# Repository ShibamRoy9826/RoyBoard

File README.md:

# RoyBoard 

## Description

Its a mechanical keyboard that I made from scratch! Its basically a 75% tenkeyless keyboard with 81 keys in total, with 3 additional rotary encoders for different tasks such as volume control, brightness control and scrolling, of course these functionalities are subject to change. It has a few neopixels too! not per key RGB though, because i rarely use backlight and it was pretty daunting to route them up, considering the fact that i just started hardware back then, the ones which I have are meant for aesthetics. Currently, I have dropped the plan to solder them because I mirrored the pinouts and it will be a terrible mess to solder them, I guess I am still satisfied with how it turned out though. 

## Features 

- ~Includes RGB lights (not per key RGB)~ (Not soldered)
- Has 3 rotary encoders for different functions
    - Media playback
    - Brightness
    - Volume
    - Scrolling
    - DWM tag switching(Any other wm works)
- 2 Layer keyboard (as of now, may add more in future if needed)
- Consists of 81 keys in total + 3 clickable rotary encoders, a 75%-ish Tenkeyless keyboard
- 5 degree tilt stand for a comfortable typing experience

## Real Life Pics

## Renders

Just for reference, these are the original keycaps that I would be using: [here](https://curiositycaps.in/products/vintage-poker-translucent-keycaps-set) . I changed the keycaps later on, thus the renders use a different keycap set.

### Full 3d renders (To Be Updated)
The renders don't include stand yet, as it has been recently included. I will update the repo soon.

### Bottom case

### Top plate

### Stand

### PCB 3D (Front)

### PCB 3D (Back)

### Schematic

### Layout

### PCB

### PCB Back

### PCB Front

## What tools did I use? 

- [kiCad](https://www.kicad.org/) : For PCB designing
- [shapr3d](https://www.shapr3d.com/) (Mostly) & [OnShape](https://onshape.com): For Case designing
- [keyboard-layout-editor](keyboard-layout-editor.com): For layout designing

## Firmware
Written in QMK, I have shifted the firmware to another repository, so please check that out [here](https://github.com/ShibamRoy9826/RoyBoard-firmware)

## 3D models

You can check the 3d models out in this [public document of OnShape](https://cad.onshape.com/documents/ddc280e53ddd9ad94dbb1da3/w/e89386a56beb1bd36360f18a/e/ed9d1e719b4e163eef3ebe0b?renderMode=0&uiState=6905da6719ceb1e5cc223bec)

## Dimensions

The entire keyboard is **385.65mm** x **166mm** (153 without the branding part) x **13mm**(+13.527mm with stand)

## Bill of materials

| Item name                             |   Net Price(USD) |   Net Price(INR) |   Expected Net Price (INR) |   Diff (INR) |
|:--------------------------------------|-----------------:|-----------------:|---------------------------:|-------------:|
| Vintage Poker Translucent Keycaps Set |            18.2  |          1599    |                    1615.98 |       -16.98 |
| Raspberry PI PICO                     |             5.06 |           449    |                     449.28 |        -0.28 |
| 1N4148 THT Diodes                     |             2.13 |           189    |                     189.12 |        -0.12 |
| EC11 Rotary Encoders                  |             4.48 |           406    |                     397.78 |         8.22 |
| Gateron Weightlessness Switches       |            39.53 |          3510    |                    3509.87 |         0.13 |
| Durock Smokey Screw-In Stabilizers v2 |            18.13 |          1595    |                    1609.76 |       -14.76 |
| PCB                                   |            66    |          5860    |                    5860.14 |        -0.14 |
| SK6812 MINI-E LEDs                    |             7.62 |           669.59 |                     676.58 |        -6.99 |
| M2 x 6 mm Heat inserts                |             1.29 |           114.6  |                     114.54 |         0.06 |
| M2 x 6 mm screws                      |           nan    |           nan    |                     nan    |       nan    |
| 3D Prints                             |           nan    |           nan    |                     nan    |       nan    |

**Total:** $162.44 (14,423 INR)

## To-Do 
- [x] ~Build it irl~
- [x] ~Do testing~
- [x] ~Upload new pics here~

## Contributing

Everyone is welcome to contribute to the code!
You can also raise an issue, or suggest any features that you think would be great :)

## License
Licensed under the MIT License. See [LICENSE](LICENSE) for more information.

> ✨ Please star this repository if you liked this project 😁

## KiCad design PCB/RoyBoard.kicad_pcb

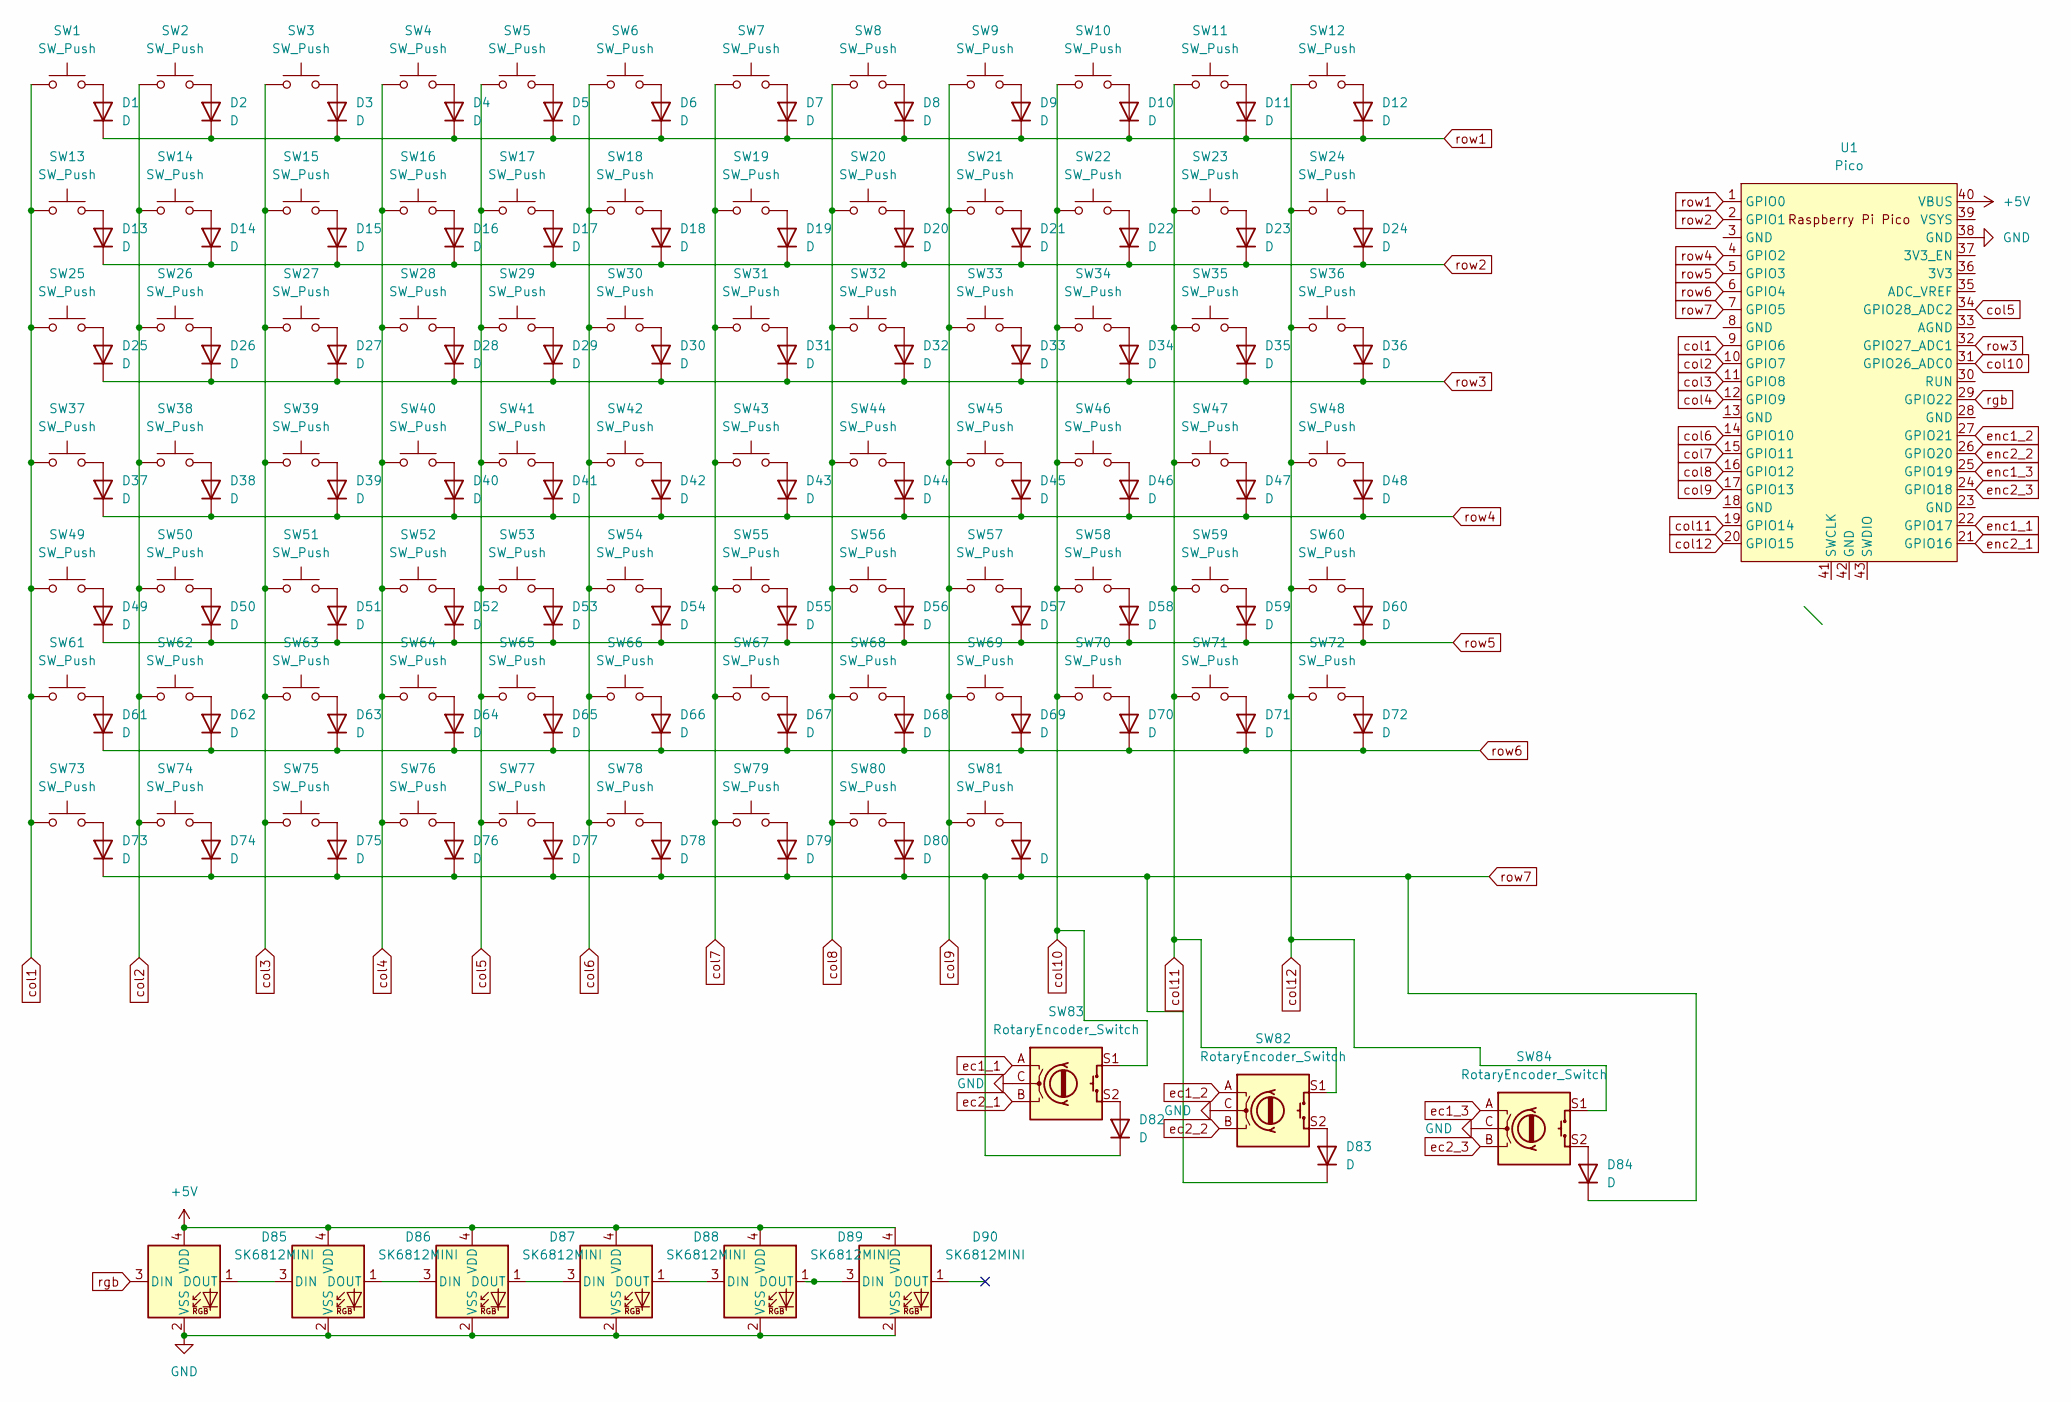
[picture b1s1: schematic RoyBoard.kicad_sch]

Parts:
D1, D2, D3, D4, D5, D6, D7, D8, D9, D10, D11, D12, D13, D14, D15, D16, D17, D18, D19, D20, D21, D22, D23, D24, D25, D26, D27, D28, D29, D30, D31, D32, D33, D34, D35, D36, D37, D38, D39, D40, D41, D42, D43, D44, D45, D46, D47, D48, D49, D50, D51, D52, D53, D54, D55, D56, D57, D58, D59, D60, D61, D62, D63, D64, D65, D66, D67, D68, D69, D70, D71, D72, D73, D74, D75, D76, D77, D78, D79, D80, D81, D82, D83, D84: D; Diode_DO-35
D85, D86, D87, D88, D89, D90: SK6812MINI; LED_SK6812MINI_PLCC4_3.5x3.5mm_P1.75mm
SW1, SW2, SW3, SW4, SW5, SW6, SW7, SW8, SW9, SW10, SW11, SW12, SW13, SW14, SW15, SW16, SW17, SW18, SW19, SW20, SW21, SW22, SW23, SW24, SW25, SW26, SW29, SW30, SW31, SW32, SW33, SW34, SW35, SW36, SW37, SW38, SW39, SW40, SW43, SW44, SW45, SW46, SW47, SW48, SW49, SW50, SW51, SW52, SW53, SW56, SW57, SW58, SW59, SW60, SW61, SW62, SW63, SW64, SW65, SW75, SW76, SW77, SW78, SW79, SW80, SW81: SW_Push; SW_Cherry_MX_1.00u_PCB
SW27: SW_Push; SW_Cherry_MX_PCB_2.00u
SW28, SW41: SW_Push; SW_Cherry_MX_PCB_1.50u
SW42: SW_Push; SW_Cherry_MX_PCB_1.75u
SW54, SW55: SW_Push; SW_Cherry_MX_2.25u_PCB
SW66: SW_Push; SW_Cherry_MX_2.75u_PCB
SW67: SW_Push; SW_Cherry_MX_1.25u_PCB
SW68, SW69, SW71, SW72, SW73, SW74: SW_Push; SW_Cherry_MX_PCB_1.25u
SW70: SW_Push; SW_Cherry_MX_6.25u_PCB
SW82, SW83, SW84: RotaryEncoder_Switch; RotaryEncoder_Alps_EC12E-Switch_Vertical_H20mm_CircularMoun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
U1: Pico; RPi_Pico_SMD_TH

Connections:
+5V: D85.4 (VDD), D86.4 (VDD), D87.4 (VDD), D88.4 (VDD), D89.4 (VDD), D90.4 (VDD), U1.40 (VBUS)
GND: D85.2 (VSS), D86.2 (VSS), D87.2 (VSS), D88.2 (VSS), D89.2 (VSS), D90.2 (VSS), SW82.C, SW83.C, SW84.C, U1.38 (GND)
unnamed: D1.2 (A), SW1.2
unnamed: D2.2 (A), SW2.2
unnamed: D3.2 (A), SW3.2
unnamed: D4.2 (A), SW4.2
unnamed: D5.2 (A), SW5.2
unnamed: D6.2 (A), SW6.2
unnamed: D7.2 (A), SW7.2
unnamed: D8.2 (A), SW8.2
unnamed: D9.2 (A), SW9.2
unnamed: D10.2 (A), SW10.2
unnamed: D11.2 (A), SW11.2
unnamed: D12.2 (A), SW12.2
unnamed: D13.2 (A), SW13.2
unnamed: D14.2 (A), SW14.2
unnamed: D15.2 (A), SW15.2
unnamed: D16.2 (A), SW16.2
unnamed: D17.2 (A), SW17.2
unnamed: D18.2 (A), SW18.2
unnamed: D19.2 (A), SW19.2
unnamed: D20.2 (A), SW20.2
unnamed: D21.2 (A), SW21.2
unnamed: D22.2 (A), SW22.2
unnamed: D23.2 (A), SW23.2
unnamed: D24.2 (A), SW24.2
unnamed: D25.2 (A), SW25.2
unnamed: D26.2 (A), SW26.2
unnamed: D27.2 (A), SW27.2
unnamed: D28.2 (A), SW28.2
unnamed: D29.2 (A), SW29.2
unnamed: D30.2 (A), SW30.2
unnamed: D31.2 (A), SW31.2
unnamed: D32.2 (A), SW32.2
unnamed: D33.2 (A), SW33.2
unnamed: D34.2 (A), SW34.2
unnamed: D35.2 (A), SW35.2
unnamed: D36.2 (A), SW36.2
unnamed: D37.2 (A), SW37.2
unnamed: D38.2 (A), SW38.2
unnamed: D39.2 (A), SW39.2
unnamed: D40.2 (A), SW40.2
unnamed: D41.2 (A), SW41.2
unnamed: D42.2 (A), SW42.2
unnamed: D43.2 (A), SW43.2
unnamed: D44.2 (A), SW44.2
unnamed: D45.2 (A), SW45.2
unnamed: D46.2 (A), SW46.2
unnamed: D47.2 (A), SW47.2
unnamed: D48.2 (A), SW48.2
unnamed: D49.2 (A), SW49.2
unnamed: D50.2 (A), SW50.2
unnamed: D51.2 (A), SW51.2
unnamed: D52.2 (A), SW52.2
unnamed: D53.2 (A), SW53.2
unnamed: D54.2 (A), SW54.2
unnamed: D55.2 (A), SW55.2
unnamed: D56.2 (A), SW56.2
unnamed: D57.2 (A), SW57.2
unnamed: D58.2 (A), SW58.2
unnamed: D59.2 (A), SW59.2
unnamed: D60.2 (A), SW60.2
unnamed: D61.2 (A), SW61.2
unnamed: D62.2 (A), SW62.2
unnamed: D63.2 (A), SW63.2
unnamed: D64.2 (A), SW64.2
unnamed: D65.2 (A), SW65.2
unnamed: D66.2 (A), SW66.2
unnamed: D67.2 (A), SW67.2
unnamed: D68.2 (A), SW68.2
unnamed: D69.2 (A), SW69.2
unnamed: D70.2 (A), SW70.2
unnamed: D71.2 (A), SW71.2
unnamed: D72.2 (A), SW72.2
unnamed: D73.2 (A), SW73.2
unnamed: D74.2 (A), SW74.2
unnamed: D75.2 (A), SW75.2
unnamed: D76.2 (A), SW76.2
unnamed: D77.2 (A), SW77.2
unnamed: D78.2 (A), SW78.2
unnamed: D79.2 (A), SW79.2
unnamed: D80.2 (A), SW80.2
unnamed: D81.2 (A), SW81.2
unnamed: D82.2 (A), SW83.S2
unnamed: D83.2 (A), SW82.S2
unnamed: D84.2 (A), SW84.S2
unnamed: D85.1 (DOUT), D86.3 (DIN)
unnamed: D86.1 (DOUT), D87.3 (DIN)
unnamed: D87.1 (DOUT), D88.3 (DIN)
unnamed: D88.1 (DOUT), D89.3 (DIN)
unnamed: D89.1 (DOUT), D90.3 (DIN)
col1: SW1.1, SW13.1, SW25.1, SW37.1, SW49.1, SW61.1, SW73.1, U1.9 (GPIO6)
col2: SW2.1, SW14.1, SW26.1, SW38.1, SW50.1, SW62.1, SW74.1, U1.10 (GPIO7)
col3: SW3.1, SW15.1, SW27.1, SW39.1, SW51.1, SW63.1, SW75.1, U1.11 (GPIO8)
col4: SW4.1, SW16.1, SW28.1, SW40.1, SW52.1, SW64.1, SW76.1, U1.12 (GPIO9)
col5: SW5.1, SW17.1, SW29.1, SW41.1, SW53.1, SW65.1, SW77.1, U1.34 (GPIO28_ADC2)
col6: SW6.1, SW18.1, SW30.1, SW42.1, SW54.1, SW66.1, SW78.1, U1.14 (GPIO10)
col7: SW7.1, SW19.1, SW31.1, SW43.1, SW55.1, SW67.1, SW79.1, U1.15 (GPIO11)
col8: SW8.1, SW20.1, SW32.1, SW44.1, SW56.1, SW68.1, SW80.1, U1.16 (GPIO12)
col9: SW9.1, SW21.1, SW33.1, SW45.1, SW57.1, SW69.1, SW81.1, U1.17 (GPIO13)
col10: SW10.1, SW22.1, SW34.1, SW46.1, SW58.1, SW70.1, SW83.S1, U1.31 (GPIO26_ADC0)
col11: SW11.1, SW23.1, SW35.1, SW47.1, SW59.1, SW71.1, SW82.S1, U1.19 (GPIO14)
col12: SW12.1, SW24.1, SW36.1, SW48.1, SW60.1, SW72.1, SW84.S1, U1.20 (GPIO15)
ec1_1: SW83.A
ec1_2: SW82.A
ec1_3: SW84.A
ec2_1: SW83.B
ec2_2: SW82.B
ec2_3: SW84.B
enc1_1: U1.22 (GPIO17)
enc1_2: U1.27 (GPIO21)
enc1_3: U1.25 (GPIO19)
enc2_1: U1.21 (GPIO16)
enc2_2: U1.26 (GPIO20)
enc2_3: U1.24 (GPIO18)
rgb: D85.3 (DIN), U1.29 (GPIO22)
row1: D1.1 (K), D2.1 (K), D3.1 (K), D4.1 (K), D5.1 (K), D6.1 (K), D7.1 (K), D8.1 (K), D9.1 (K), D10.1 (K), D11.1 (K), D12.1 (K), U1.1 (GPIO0)
row2: D13.1 (K), D14.1 (K), D15.1 (K), D16.1 (K), D17.1 (K), D18.1 (K), D19.1 (K), D20.1 (K), D21.1 (K), D22.1 (K), D23.1 (K), D24.1 (K), U1.2 (GPIO1)
row3: D25.1 (K), D26.1 (K), D27.1 (K), D28.1 (K), D29.1 (K), D30.1 (K), D31.1 (K), D32.1 (K), D33.1 (K), D34.1 (K), D35.1 (K), D36.1 (K), U1.32 (GPIO27_ADC1)
row4: D37.1 (K), D38.1 (K), D39.1 (K), D40.1 (K), D41.1 (K), D42.1 (K), D43.1 (K), D44.1 (K), D45.1 (K), D46.1 (K), D47.1 (K), D48.1 (K), U1.4 (GPIO2)
row5: D49.1 (K), D50.1 (K), D51.1 (K), D52.1 (K), D53.1 (K), D54.1 (K), D55.1 (K), D56.1 (K), D57.1 (K), D58.1 (K), D59.1 (K), D60.1 (K), U1.5 (GPIO3)
row6: D61.1 (K), D62.1 (K), D63.1 (K), D64.1 (K), D65.1 (K), D66.1 (K), D67.1 (K), D68.1 (K), D69.1 (K), D70.1 (K), D71.1 (K), D72.1 (K), U1.6 (GPIO4)
row7: D73.1 (K), D74.1 (K), D75.1 (K), D76.1 (K), D77.1 (K), D78.1 (K), D79.1 (K), D80.1 (K), D81.1 (K), D82.1 (K), D83.1 (K), D84.1 (K), U1.7 (GPIO5)

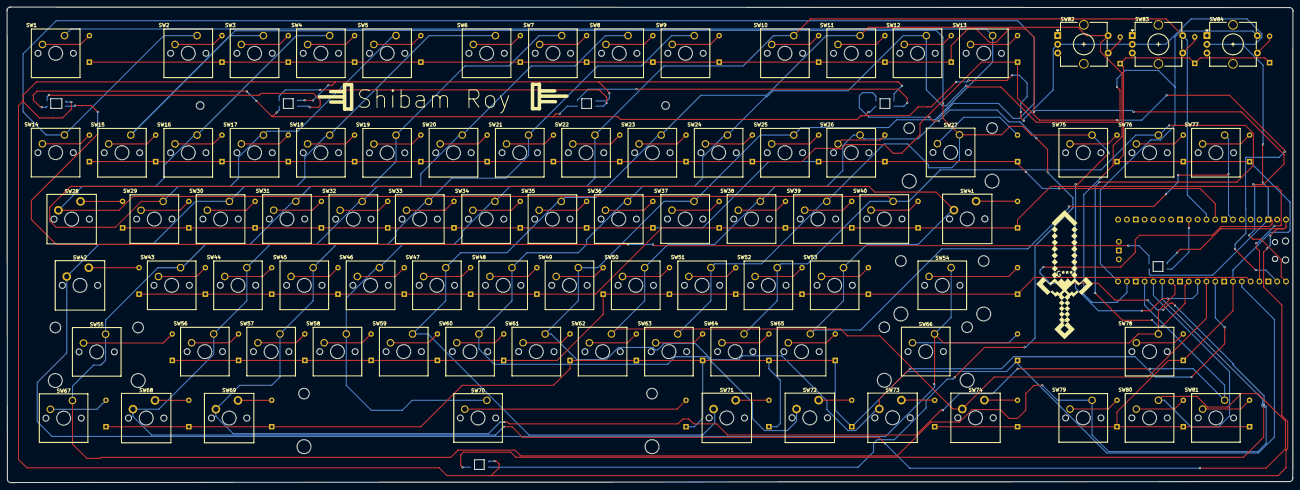
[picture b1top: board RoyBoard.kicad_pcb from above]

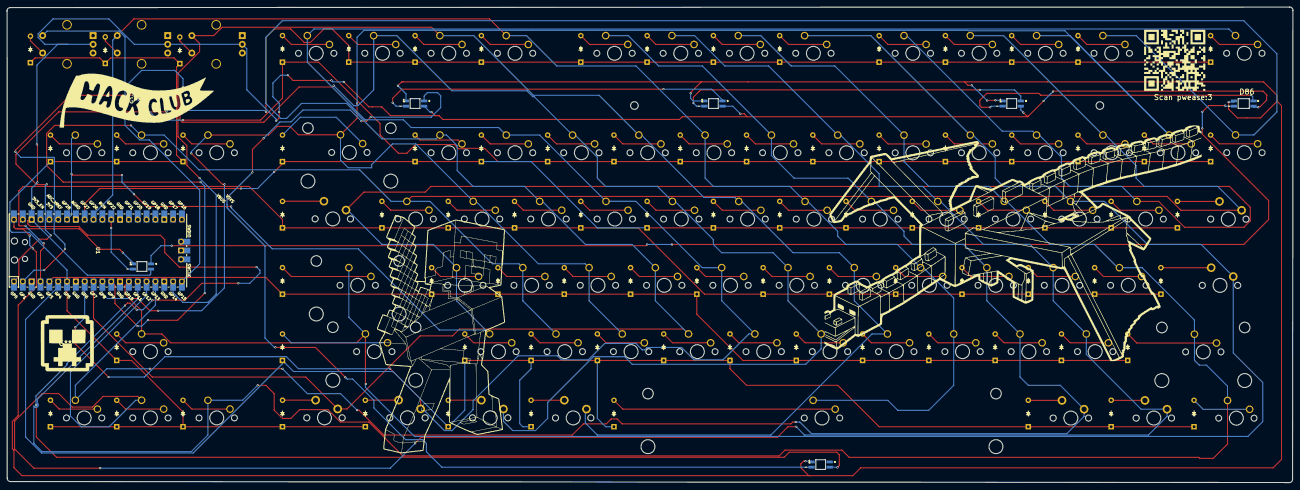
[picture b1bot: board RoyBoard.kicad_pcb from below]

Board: 2 copper layers, 369.5 x 136.6 mm, 175 parts (91 on the bottom side), 111 nets.

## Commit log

2025-03-27 Completed keyboard
2025-03-27 Restructured everything
2025-06-10 Added readme and changed silkscreen
2025-06-10 Fixed images in readme
2025-06-10 Changed screenshot path
2025-06-10 Update README.md
    removed some unnecessary text
2025-06-27 Added CAD models, firmware and 3d renders
2025-06-27 Added BOM and layout
2025-06-27 Added BOM in csv format, and updated readme
2025-10-16 Added new minecraft themed silkscreen
2025-10-16 added new screenshots and removed unncessary images
2025-10-16 Updated prices
2025-10-17 Updated description
2025-10-17 Added new screenshots
2025-10-17 Updated switches
2025-10-17 Updated CSV
2025-10-23 Updated BOM
2025-10-23 updated footprints to SK6812MINI-E
2025-10-23 added full renders
2025-10-23 Updated CSV BOM
2025-10-23 Fixed total price positions
2025-10-23 Fixed INR total
2025-10-24 Fixed keycap links
    Had a wrong keycap set link earlier
2025-10-24 Fixed typo
2025-11-01 track step files with Git LFS
2025-11-01 added other files with lfs tracking
2025-11-01 Added new gerbers
2025-11-01 Create LICENSE
2026-04-20 Removed firmware, added irl pics

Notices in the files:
README.md:
License: MIT
